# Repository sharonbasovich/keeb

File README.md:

# Sharon's Keeb

A custom 65% keyboard with two knobs and two function layers to maximize my productivity.

## Why did I make this?

Apart from improving at CAD, KiCAD, programming, and soldering, my goal with this project was to make a keyboard that matched my preferences (such as two knobs) and could be made with readily available components. It uses standard switches, diodes, and encoders. Also, everything is THT which means I can use it to teach my friends soldering (like I did with my extra hackpad PCBs).

## Layers
### The FN1 key toggles to  a F1-12 and navigation layer
### The FN2 key toggles to a media control layer

# Key Matrix Table
### Rotary Encoder #1: Volume Up/Down and Play/Pause
### Rotary Encoder #2: Zoom In/Out and Win + Shift + S (Snipping Tool)

| Row | C1   | C2   | C3   | C4 | C5 | C6 | C7    | C8 | C9 | C10  | C11 | C12  | C13   | C14  | C15  |
| --- | ---- | ---- | ---- | -- | -- | -- | ----- | -- | -- | ---- | --- | ---- | ----- | ---- | ---- |
| R1  | ESC  | 1    | 2    | 3  | 4  | 5  | 6     | 7  | 8  | 9    | 0   | -    | =     | BSPC | DEL  |
| R2  | TAB  | Q    | W    | E  | R  | T  | Y     | U  | I  | O    | P   | \[   | ]     | BSLS | HOME |
| R3  | CAPS | A    | S    | D  | F  | G  | H     | J  | K  | L    | ;   | '    | ENTER | N/A   | PGUP |
| R4  | LSFT | Z    | X    | C  | V  | B  | N     | M  | ,  | .    | /   | RSFT | UP    | N/A   | PGDN |
| R5  | LCTL | LGUI | LALT | N/A | N/A | N/A | SPACE | N/A | N/A | RALT | FN1 | FN2  | LEFT  | DOWN | RGHT |

# Bill of Materials

| Item                                | Quantity | Link                                                                                       | Price |
|-------------------------------------|----------|--------------------------------------------------------------------------------------------|-------|
| Raspberry Pi Pico                   | 1        | https://amazon.com/dp/B09KVB8LVR                                                           | 8.14  |
| Key Switches (JWICK Ultimate Black) | 68       | https://www.amazon.com/Ultimate-Switch-Switches-Mechanical-Keyboard/dp/B0C391QDFB/?th=1    | 19.99 |
| 1N4148 Diodes                       | 68       | https://www.amazon.com/McIgIcM-1n4148-switching-Standard-Through/dp/B06XB1R2NK/            | 4.99  |
| EC11 Rotary Encoder                 | 2        | https://www.amazon.com/Original-Rotary-Encoder-Digital-Potentiometer/dp/B07VP4847G/        | 3.10  |
| Keycaps                             | 68       | https://www.amazon.ca/Keycaps-Doubleshot-Switches-Mechanical-Keyboard/dp/B0D6QXTZT4/       | 35.99 |
| Stabilizers                         | 5        | https://www.amazon.com/DUROCK-Stabilizer-Innovative-Pre-clipped-Stabilizers/dp/B0D4QF6TGB/ | 9.99  |
| PCB                                 | 1        | https://jlcpcb.com/                                                                        | 24.30 |
| Case Bottom                         | 1        | None, 3DP at home                                                                          |       |
| Case Top                            | 1        | None, 3DP at home                                                                          |       |

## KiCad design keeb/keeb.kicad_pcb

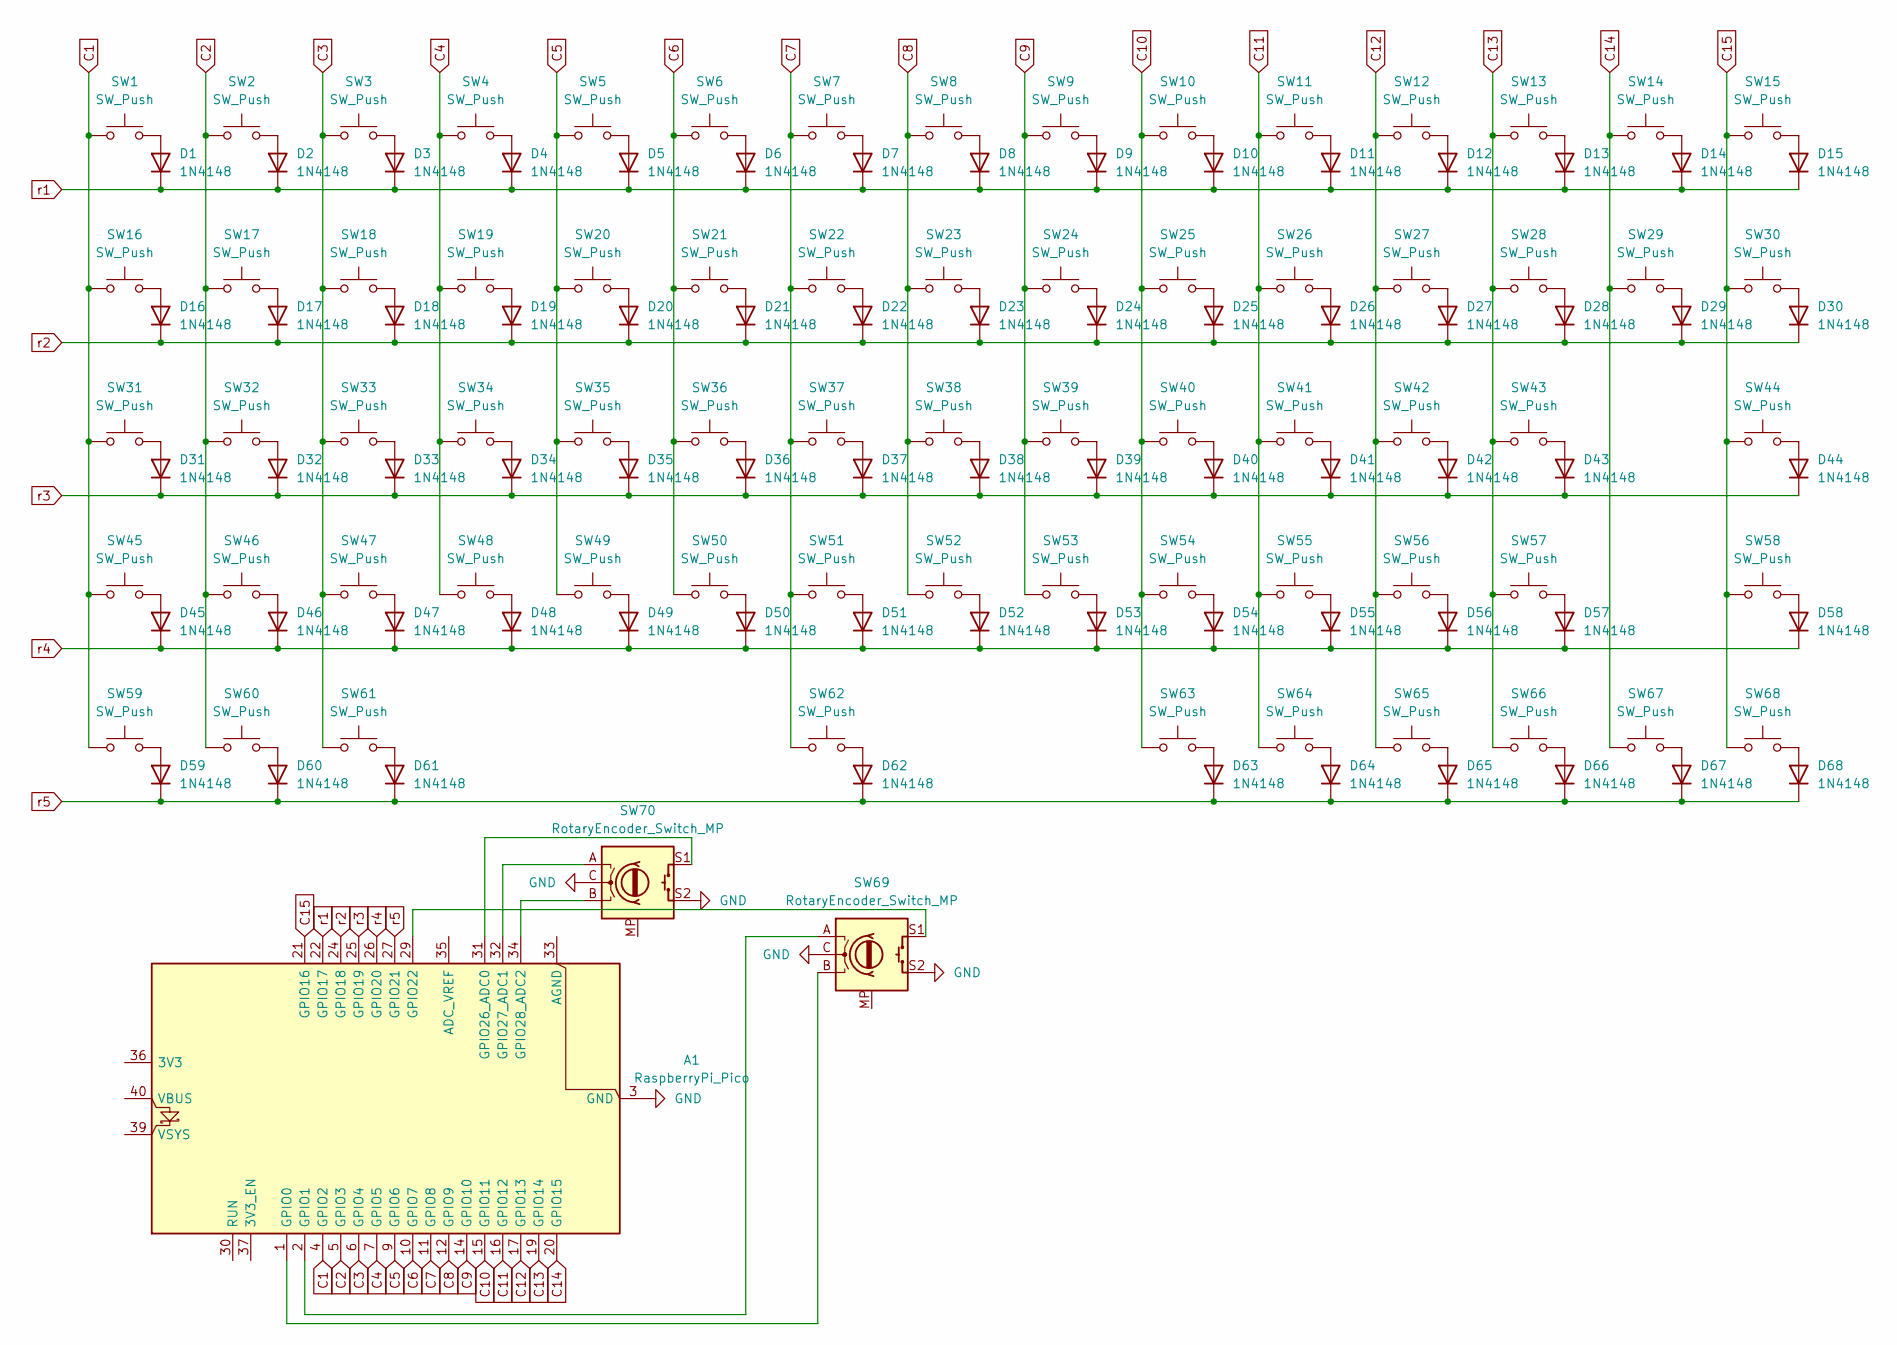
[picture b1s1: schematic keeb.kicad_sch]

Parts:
A1: RaspberryPi_Pico; RaspberryPi_Pico_Common_THT
D1, D2, D3, D4, D5, D6, D7, D8, D9, D10, D11, D12, D13, D14, D15, D16, D17, D18, D19, D20, D21, D22, D23, D24, D25, D26, D27, D28, D29, D30, D31, D32, D33, D34, D35, D36, D37, D38, D39, D40, D41, D42, D43, D44, D45, D46, D47, D48, D49, D50, D51, D52, D53, D54, D55, D56, D57, D58, D59, D60, D61, D62, D63, D64, D65, D66, D67, D68: 1N4148; D_DO-35_SOD27_P7.62mm_Horizontal
SW1, SW2, SW3, SW4, SW5, SW6, SW7, SW8, SW9, SW10, SW11, SW12, SW13, SW14, SW15, SW16, SW17, SW18, SW19, SW20, SW21, SW22, SW23, SW24, SW25, SW26, SW27, SW28, SW29, SW30, SW31, SW32, SW33, SW34, SW35, SW36, SW37, SW38, SW39, SW40, SW41, SW42, SW43, SW44, SW45, SW46, SW47, SW48, SW49, SW50, SW51, SW52, SW53, SW54, SW55, SW56, SW57, SW58, SW59, SW60, SW61, SW62, SW63, SW64, SW65, SW66, SW67, SW68: SW_Push; SW_Cherry_MX_1.00u_PCB_Sharon
SW69, SW70: RotaryEncoder_Switch_MP; Encoder_EC11_MX

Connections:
C1: A1.4 (GPIO2), SW1.1, SW16.1, SW31.1, SW45.1, SW59.1
C2: A1.5 (GPIO3), SW2.1, SW17.1, SW32.1, SW46.1, SW60.1
C3: A1.6 (GPIO4), SW3.1, SW18.1, SW33.1, SW47.1, SW61.1
C4: A1.7 (GPIO5), SW4.1, SW19.1, SW34.1, SW48.1
C5: A1.9 (GPIO6), SW5.1, SW20.1, SW35.1, SW49.1
C6: A1.10 (GPIO7), SW6.1, SW21.1, SW36.1, SW50.1
C7: A1.11 (GPIO8), SW7.1, SW22.1, SW37.1, SW51.1, SW62.1
C8: A1.12 (GPIO9), SW8.1, SW23.1, SW38.1, SW52.1
C9: A1.14 (GPIO10), SW9.1, SW24.1, SW39.1, SW53.1
C10: A1.15 (GPIO11), SW10.1, SW25.1, SW40.1, SW54.1, SW63.1
C11: A1.16 (GPIO12), SW11.1, SW26.1, SW41.1, SW55.1, SW64.1
C12: A1.17 (GPIO13), SW12.1, SW27.1, SW42.1, SW56.1, SW65.1
C13: A1.19 (GPIO14), SW13.1, SW28.1, SW43.1, SW57.1, SW66.1
C14: A1.20 (GPIO15), SW14.1, SW29.1, SW67.1
C15: A1.21 (GPIO16), SW15.1, SW30.1, SW44.1, SW58.1, SW68.1
GND: A1.3 (GND), A1.8 (GND), A1.13 (GND), A1.18 (GND), A1.23 (GND), A1.28 (GND), A1.38 (GND), SW69.C, SW69.S2, SW70.C, SW70.S2
unnamed: A1.1 (GPIO0), SW69.B
unnamed: A1.2 (GPIO1), SW69.A
unnamed: A1.29 (GPIO22), SW69.S1
unnamed: A1.31 (GPIO26_ADC0), SW70.S1
unnamed: A1.32 (GPIO27_ADC1), SW70.A
unnamed: A1.34 (GPIO28_ADC2), SW70.B
unnamed: D1.2 (A), SW1.2
unnamed: D2.2 (A), SW2.2
unnamed: D3.2 (A), SW3.2
unnamed: D4.2 (A), SW4.2
unnamed: D5.2 (A), SW5.2
unnamed: D6.2 (A), SW6.2
unnamed: D7.2 (A), SW7.2
unnamed: D8.2 (A), SW8.2
unnamed: D9.2 (A), SW9.2
unnamed: D10.2 (A), SW10.2
unnamed: D11.2 (A), SW11.2
unnamed: D12.2 (A), SW12.2
unnamed: D13.2 (A), SW13.2
unnamed: D14.2 (A), SW14.2
unnamed: D15.2 (A), SW15.2
unnamed: D16.2 (A), SW16.2
unnamed: D17.2 (A), SW17.2
unnamed: D18.2 (A), SW18.2
unnamed: D19.2 (A), SW19.2
unnamed: D20.2 (A), SW20.2
unnamed: D21.2 (A), SW21.2
unnamed: D22.2 (A), SW22.2
unnamed: D23.2 (A), SW23.2
unnamed: D24.2 (A), SW24.2
unnamed: D25.2 (A), SW25.2
unnamed: D26.2 (A), SW26.2
unnamed: D27.2 (A), SW27.2
unnamed: D28.2 (A), SW28.2
unnamed: D29.2 (A), SW29.2
unnamed: D30.2 (A), SW30.2
unnamed: D31.2 (A), SW31.2
unnamed: D32.2 (A), SW32.2
unnamed: D33.2 (A), SW33.2
unnamed: D34.2 (A), SW34.2
unnamed: D35.2 (A), SW35.2
unnamed: D36.2 (A), SW36.2
unnamed: D37.2 (A), SW37.2
unnamed: D38.2 (A), SW38.2
unnamed: D39.2 (A), SW39.2
unnamed: D40.2 (A), SW40.2
unnamed: D41.2 (A), SW41.2
unnamed: D42.2 (A), SW42.2
unnamed: D43.2 (A), SW43.2
unnamed: D44.2 (A), SW44.2
unnamed: D45.2 (A), SW45.2
unnamed: D46.2 (A), SW46.2
unnamed: D47.2 (A), SW47.2
unnamed: D48.2 (A), SW48.2
unnamed: D49.2 (A), SW49.2
unnamed: D50.2 (A), SW50.2
unnamed: D51.2 (A), SW51.2
unnamed: D52.2 (A), SW52.2
unnamed: D53.2 (A), SW53.2
unnamed: D54.2 (A), SW54.2
unnamed: D55.2 (A), SW55.2
unnamed: D56.2 (A), SW56.2
unnamed: D57.2 (A), SW57.2
unnamed: D58.2 (A), SW58.2
unnamed: D59.2 (A), SW59.2
unnamed: D60.2 (A), SW60.2
unnamed: D61.2 (A), SW61.2
unnamed: D62.2 (A), SW62.2
unnamed: D63.2 (A), SW63.2
unnamed: D64.2 (A), SW64.2
unnamed: D65.2 (A), SW65.2
unnamed: D66.2 (A), SW66.2
unnamed: D67.2 (A), SW67.2
unnamed: D68.2 (A), SW68.2
r1: A1.22 (GPIO17), D1.1 (K), D2.1 (K), D3.1 (K), D4.1 (K), D5.1 (K), D6.1 (K), D7.1 (K), D8.1 (K), D9.1 (K), D10.1 (K), D11.1 (K), D12.1 (K), D13.1 (K), D14.1 (K), D15.1 (K)
r2: A1.24 (GPIO18), D16.1 (K), D17.1 (K), D18.1 (K), D19.1 (K), D20.1 (K), D21.1 (K), D22.1 (K), D23.1 (K), D24.1 (K), D25.1 (K), D26.1 (K), D27.1 (K), D28.1 (K), D29.1 (K), D30.1 (K)
r3: A1.25 (GPIO19), D31.1 (K), D32.1 (K), D33.1 (K), D34.1 (K), D35.1 (K), D36.1 (K), D37.1 (K), D38.1 (K), D39.1 (K), D40.1 (K), D41.1 (K), D42.1 (K), D43.1 (K), D44.1 (K)
r4: A1.26 (GPIO20), D45.1 (K), D46.1 (K), D47.1 (K), D48.1 (K), D49.1 (K), D50.1 (K), D51.1 (K), D52.1 (K), D53.1 (K), D54.1 (K), D55.1 (K), D56.1 (K), D57.1 (K), D58.1 (K)
r5: A1.27 (GPIO21), D59.1 (K), D60.1 (K), D61.1 (K), D62.1 (K), D63.1 (K), D64.1 (K), D65.1 (K), D66.1 (K), D67.1 (K), D68.1 (K)

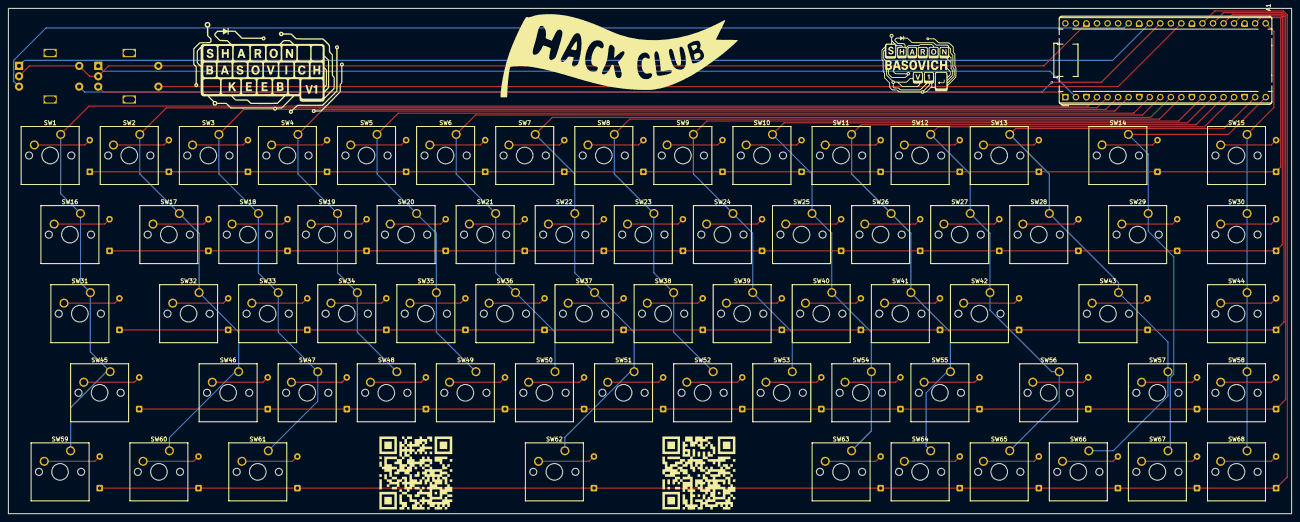
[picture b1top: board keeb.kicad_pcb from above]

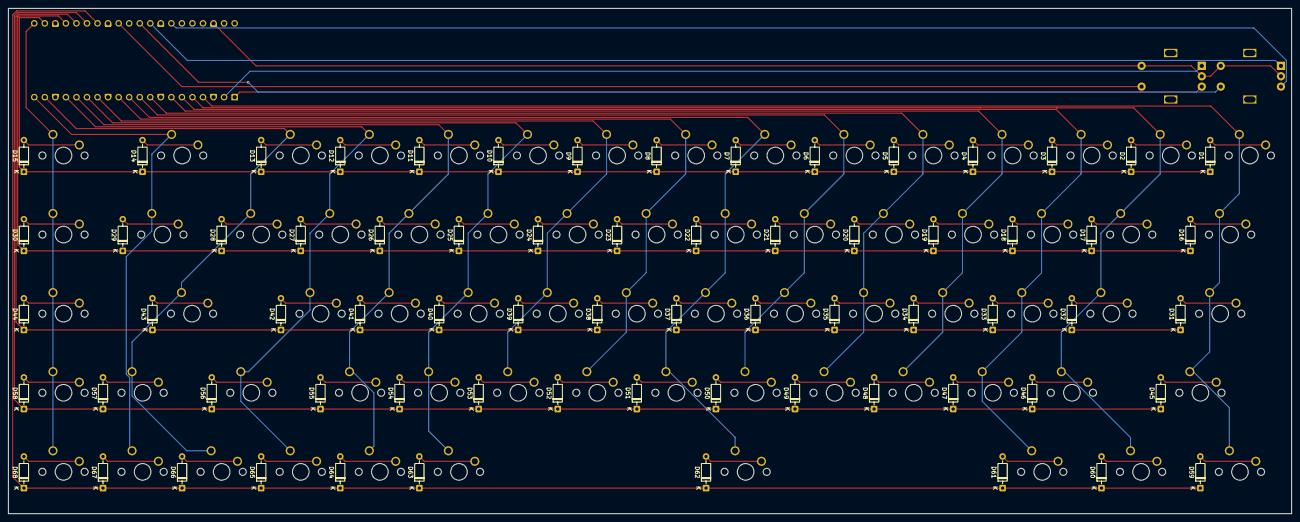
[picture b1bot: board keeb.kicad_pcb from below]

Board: 2 copper layers, 309.1 x 121.7 mm, 139 parts (68 on the bottom side), 95 nets.

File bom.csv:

Designator,Footprint,Quantity,Value,LCSC Part #
A1,RaspberryPi_Pico_Common_THT,1,RaspberryPi_Pico,
"D1, D10, D11, D12, D13, D14, D15, D16, D17, D18, D19, D2, D20, D21, D22, D23, D24, D25, D26, D27, D28, D29, D3, D30, D31, D32, D33, D34, D35, D36, D37, D38, D39, D4, D40, D41, D42, D43, D44, D45, D46, D47, D48, D49, D5, D50, D51, D52, D53, D54, D55, D56, D57, D58, D59, D6, D60, D61, D62, D63, D64, D65, D66, D67, D68, D7, D8, D9",D_DO-35_SOD27_P7.62mm_Horizontal,68,1N4148,
"SW1, SW10, SW11, SW12, SW13, SW14, SW15, SW16, SW17, SW18, SW19, SW2, SW20, SW21, SW22, SW23, SW24, SW25, SW26, SW27, SW28, SW29, SW3, SW30, SW31, SW32, SW33, SW34, SW35, SW36, SW37, SW38, SW39, SW4, SW40, SW41, SW42, SW43, SW44, SW45, SW46, SW47, SW48, SW49, SW5, SW50, SW51, SW52, SW53, SW54, SW55, SW56, SW57, SW58, SW59, SW6, SW60, SW61, SW62, SW63, SW64, SW65, SW66, SW67, SW68, SW7, SW8, SW9",SW_Cherry_MX_1.00u_PCB_Sharon,68,SW_Push,
"SW69, SW70",Encoder_EC11_MX,2,RotaryEncoder_Switch_MP,

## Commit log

2025-07-28 submission
2025-07-28 organization
2025-07-28 added schematic
2025-07-29 cleanup
2025-08-02 kmk files
2025-08-07 Updated assembly
2025-08-10 Create temp
